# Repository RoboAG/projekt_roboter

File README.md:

# projekt_roboter
Aktuelle und historische Roboter der RoboAG

Note: This repo is also part of the [repository list](https://github.com/peterweissig/bash_repo).

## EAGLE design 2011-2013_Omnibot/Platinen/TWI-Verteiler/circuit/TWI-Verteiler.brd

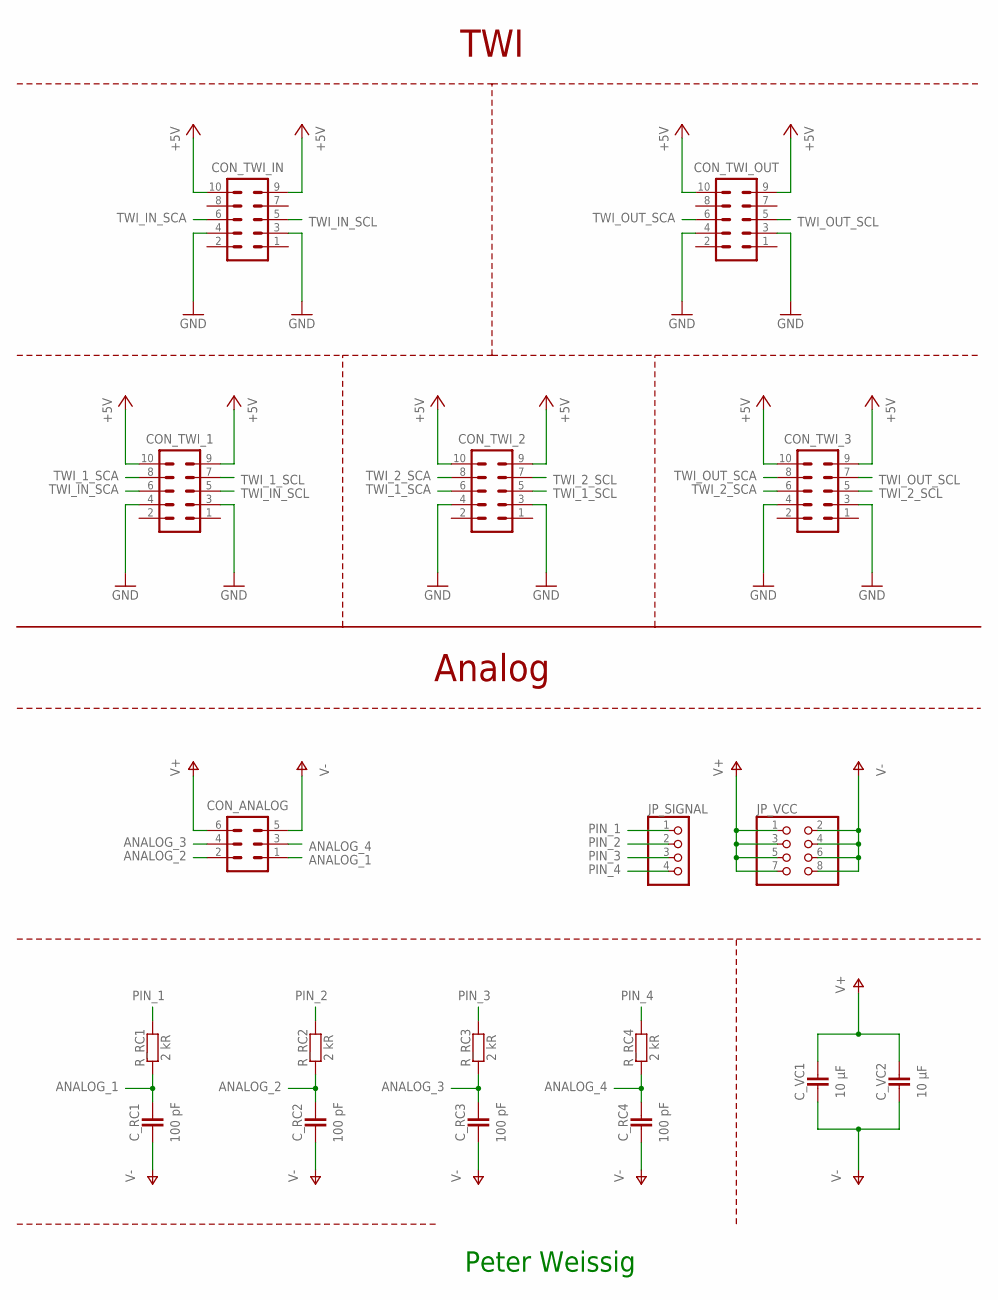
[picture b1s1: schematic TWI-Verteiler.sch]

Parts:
CON_ANALOG: STECKER_WANNE_6
CON_TWI_1, CON_TWI_2, CON_TWI_3: STECKER_WANNE_10
CON_TWI_IN: STECKER_WANNE_10
CON_TWI_OUT: STECKER_WANNE_10
C_RC1, C_RC2, C_RC3, C_RC4: 100 pF; SMD_0603
C_VC1, C_VC2: 10 µF; SMD_0603
JP_SIGNAL: PINHD-1X4; 1X04
JP_VCC: PINHD-2X4; 2X04
R_RC1, R_RC2, R_RC3, R_RC4: 2 kR; SMD_0603

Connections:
+5V: CON_TWI_1.9, CON_TWI_1.10, CON_TWI_2.9, CON_TWI_2.10, CON_TWI_3.9, CON_TWI_3.10, CON_TWI_IN.9, CON_TWI_IN.10, CON_TWI_OUT.9, CON_TWI_OUT.10
ANALOG_1: CON_ANALOG.1, C_RC1.1, R_RC1.2
ANALOG_2: CON_ANALOG.2, C_RC2.1, R_RC2.2
ANALOG_3: CON_ANALOG.4, C_RC3.1, R_RC3.2
ANALOG_4: CON_ANALOG.3, C_RC4.1, R_RC4.2
GND: CON_TWI_1.3, CON_TWI_1.4, CON_TWI_2.3, CON_TWI_2.4, CON_TWI_3.3, CON_TWI_3.4, CON_TWI_IN.3, CON_TWI_IN.4, CON_TWI_OUT.3, CON_TWI_OUT.4
PIN_1: JP_SIGNAL.1, R_RC1.1
PIN_2: JP_SIGNAL.2, R_RC2.1
PIN_3: JP_SIGNAL.3, R_RC3.1
PIN_4: JP_SIGNAL.4, R_RC4.1
TWI_1_SCA: CON_TWI_1.8, CON_TWI_2.6
TWI_1_SCL: CON_TWI_1.7, CON_TWI_2.5
TWI_2_SCA: CON_TWI_2.8, CON_TWI_3.6
TWI_2_SCL: CON_TWI_2.7, CON_TWI_3.5
TWI_IN_SCA: CON_TWI_1.6, CON_TWI_IN.6
TWI_IN_SCL: CON_TWI_1.5, CON_TWI_IN.5
TWI_OUT_SCA: CON_TWI_3.8, CON_TWI_OUT.6
TWI_OUT_SCL: CON_TWI_3.7, CON_TWI_OUT.5
V+: CON_ANALOG.6, C_VC1.1, C_VC2.1, JP_VCC.1, JP_VCC.3, JP_VCC.5, JP_VCC.7
V-: CON_ANALOG.5, C_RC1.2, C_RC2.2, C_RC3.2, C_RC4.2, C_VC1.2, C_VC2.2, JP_VCC.2, JP_VCC.4, JP_VCC.6, JP_VCC.8

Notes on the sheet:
Peter Weissig
TWI
Analog

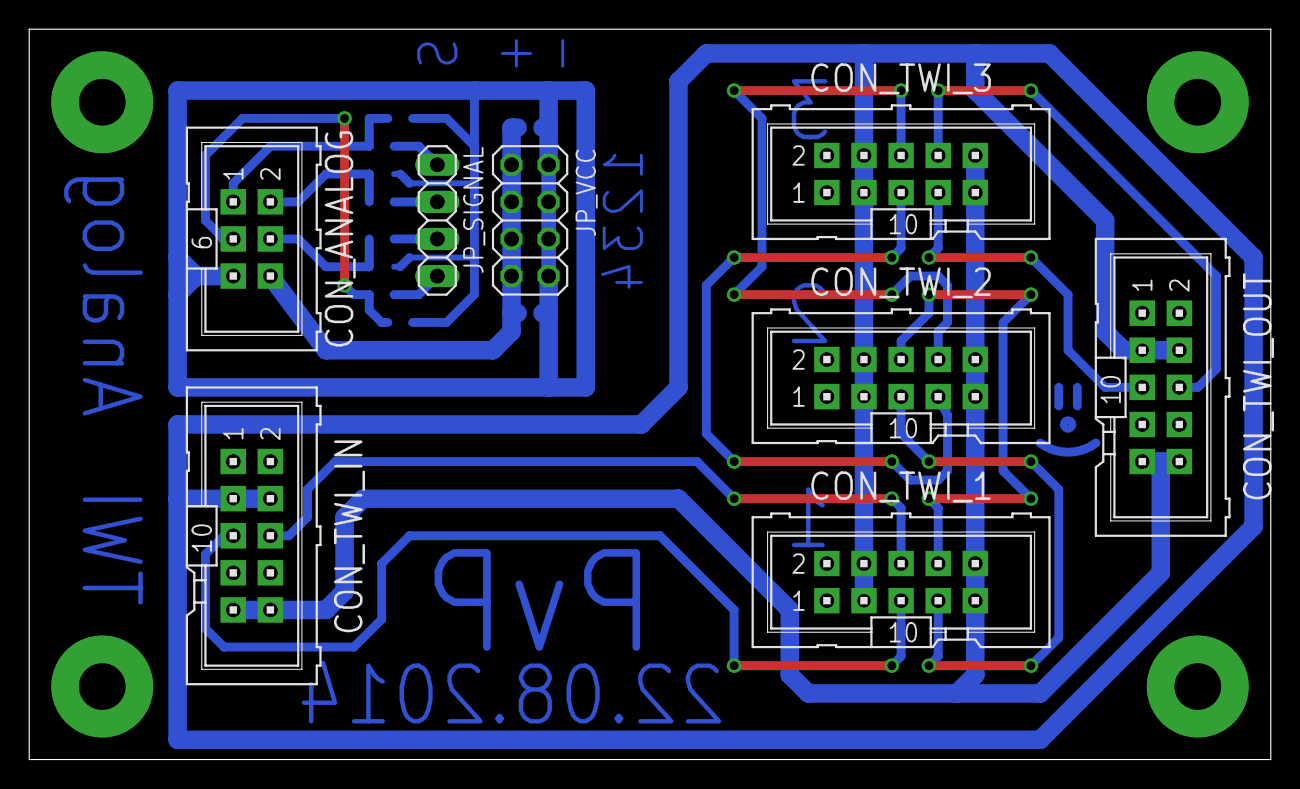
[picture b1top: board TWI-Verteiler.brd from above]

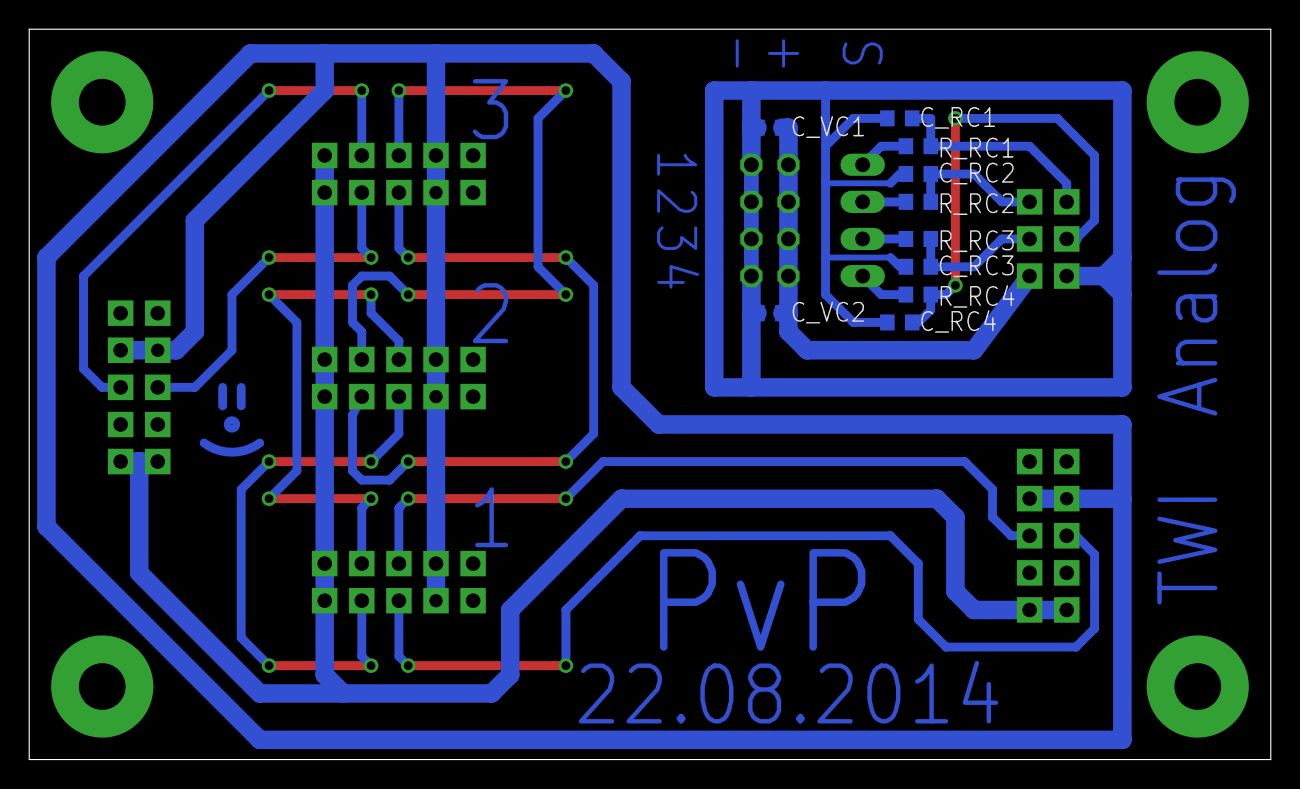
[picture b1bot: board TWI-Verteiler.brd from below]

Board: 2 copper layers, 85.0 x 50.0 mm, 18 parts (10 on the bottom side), 20 nets.

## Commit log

2018-11-02 initial commit + added RoboSAX 2017-2018
2019-02-03 added readme for RoboSAX 2017-2018
2019-02-03 updated Dokumentation
2019-02-16 added AluBot 2016 (Besondere Lernleistung von Richard Roth)
2019-02-16 added RoboSAX 2018-2019 (Versuch eines Blogs)
2019-02-16 renamed alubot to AluBot
2019-04-12 added OmniBot (2011-2013)
2019-04-28 updated Blog for RoboSAX 2018-2019 (AluBot)
2019-04-28 updated Blog 2018/2019
2019-06-22 updated RoboSAX 2019 + updated readme + added images + added source code
2019-06-22 added last working Software of OmniBot (2013-2014)
2019-06-22 updated Autoren
2019-06-22 moved Ideen.pdf from Dokumentation/ to Ideen/
2019-06-22 updated Kabel und Anschlüsse + fixed typo in folder name + added .pdf and .ods for dsub and twi explanation + removed .txt explanation of dsub and twi (they are part of the source code & there are ne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
2019-06-22 added Pinbelegung atmega
2019-06-22 minor update to TWI-Anschlussbelegung
2019-06-22 fixed source code of omnibot + added missing header + added gitignore + removed keplerboard.h from repo
2023-01-03 updated Jahr der MIT-Lizenz
2023-01-03 added Roboter 2021-2022
2023-01-07 added Quelltext für 3Pi (Schuljahr 2021-2022)
2024-11-07 updated License
2024-11-07 updated doc of previous years
2024-11-07 added missing Spielfelder for previous years
2024-11-07 added RoboSAX 2024
